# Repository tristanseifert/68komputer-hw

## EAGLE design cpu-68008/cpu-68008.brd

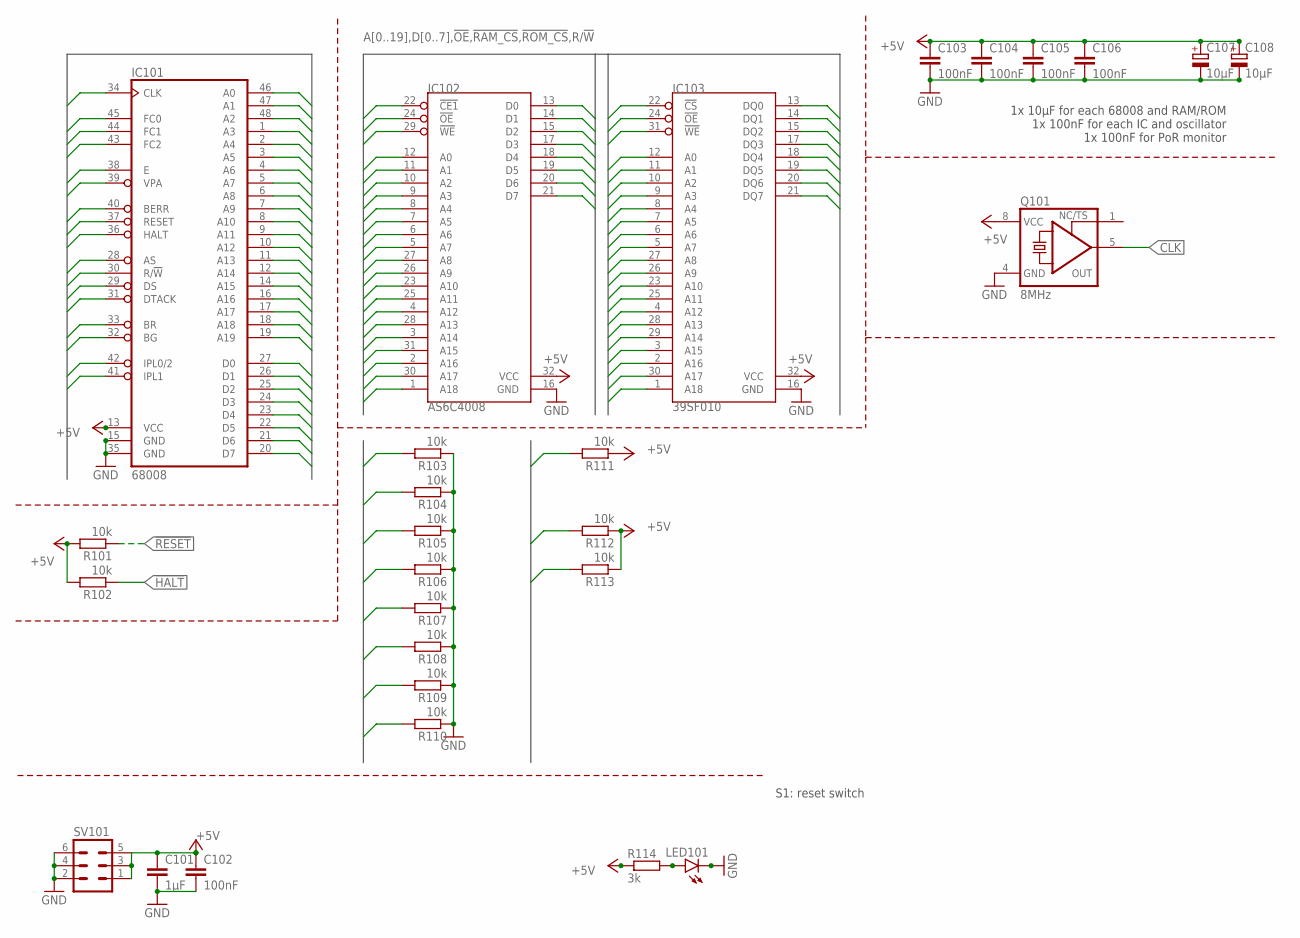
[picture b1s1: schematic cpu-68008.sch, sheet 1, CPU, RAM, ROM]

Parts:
C101: 1µF; C0805; MOUSER 710-885012107015
C102, C103, C104, C105, C106: 100nF; C0805; MOUSER 710-885012207072
C107, C108: 10µF; SMC_B; MOUSER 581-TAJB106K020RNJV
IC101: 68008; DIL48; MOUSER_SOCKET 517-4848-6004-CP
IC102: AS6C4008; DIL32; MOUSER_SOCKET 517-4832-6000-CP
IC103: 39SF010; DIL32; MOUSER 804-39SF010A7CPHE
LED101: LEDCHIPLED_1206; CHIPLED_1206; MOUSER 710-156120YS75300
Q101: 8MHz; DIL08S; MOUSER 774-MXO45HS-3C-8.0
R101, R102, R103, R104, R105, R106, R107, R108, R109, R110, R111, R112, R113: 10k; R2012; MOUSER 652-CR0805FX-1002ELF
R114: 3k; R2012; MOUSER 652-CR0805JW-302ELF
SV101: MA03-2

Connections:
!AS: IC101.28 (AS); also elsewhere on the board
!BERR: IC101.40 (BERR), R113.2; also elsewhere on the board
!BG: IC101.32 (BG); also elsewhere on the board
!BR: IC101.33 (BR), R111.2; also elsewhere on the board
!DS: IC101.29 (DS); also elsewhere on the board
!DTACK: IC101.31 (DTACK); also elsewhere on the board
!HALT: IC101.36 (HALT), R102.1; also elsewhere on the board
!IPL0/2: IC101.42 (IPL0/2); also elsewhere on the board
!IPL1: IC101.41 (IPL1); also elsewhere on the board
!OE: IC102.24 (!OE), IC103.24 (!OE); also elsewhere on the board
!RAM_CS: IC102.22 (!CE1); also elsewhere on the board
!RESET: IC101.37 (RESET), R101.1; also elsewhere on the board
!ROM_CS: IC103.22 (!CS); also elsewhere on the board
!VPA: IC101.39 (VPA), R112.2; also elsewhere on the board
+5V: C101.1, C102.1, C103.1, C104.1, C105.1, C106.1, C107.+, C108.+, IC101.13 (VCC), IC102.32 (VCC), IC103.32 (VCC), Q101.8 (VCC), R101.2, R102.2, R111.1, R112.1, R113.1, R114.1, SV101.1, SV101.3, SV101.5; also elsewhere on the board
A0: IC101.46 (A0), IC102.12 (A0), IC103.12 (A0); also elsewhere on the board
A1: IC101.47 (A1), IC102.11 (A1), IC103.11 (A1); also elsewhere on the board
A2: IC101.48 (A2), IC102.10 (A2), IC103.10 (A2); also elsewhere on the board
A3: IC101.1 (A3), IC102.9 (A3), IC103.9 (A3); also elsewhere on the board
A4: IC101.2 (A4), IC102.8 (A4), IC103.8 (A4); also elsewhere on the board
A5: IC101.3 (A5), IC102.7 (A5), IC103.7 (A5); also elsewhere on the board
A6: IC101.4 (A6), IC102.6 (A6), IC103.6 (A6); also elsewhere on the board
A7: IC101.5 (A7), IC102.5 (A7), IC103.5 (A7); also elsewhere on the board
A8: IC101.6 (A8), IC102.27 (A8), IC103.27 (A8); also elsewhere on the board
A9: IC101.7 (A9), IC102.26 (A9), IC103.26 (A9); also elsewhere on the board
A10: IC101.8 (A10), IC102.23 (A10), IC103.23 (A10); also elsewhere on the board
A11: IC101.9 (A11), IC102.25 (A11), IC103.25 (A11); also elsewhere on the board
A12: IC101.10 (A12), IC102.4 (A12), IC103.4 (A12); also elsewhere on the board
A13: IC101.11 (A13), IC102.28 (A13), IC103.28 (A13); also elsewhere on the board
A14: IC101.12 (A14), IC102.3 (A14), IC103.29 (A14); also elsewhere on the board
A15: IC101.14 (A15), IC102.31 (A15), IC103.3 (A15); also elsewhere on the board
A16: IC101.16 (A16), IC102.2 (A16), IC103.2 (A16); also elsewhere on the board
A17: IC101.17 (A17), IC102.30 (A17), IC103.30 (A17); also elsewhere on the board
A18: IC101.18 (A18), IC102.1 (A18), IC103.1 (A18); also elsewhere on the board
A19: IC101.19 (A19); also elsewhere on the board
CLK: IC101.34 (CLK), Q101.5 (OUT); also elsewhere on the board
D0: IC101.27 (D0), IC102.13 (D0), IC103.13 (DQ0), R103.2; also elsewhere on the board
D1: IC101.26 (D1), IC102.14 (D1), IC103.14 (DQ1), R104.2; also elsewhere on the board
D2: IC101.25 (D2), IC102.15 (D2), IC103.15 (DQ2), R105.2; also elsewhere on the board
D3: IC101.24 (D3), IC102.17 (D3), IC103.17 (DQ3), R106.2; also elsewhere on the board
D4: IC101.23 (D4), IC102.18 (D4), IC103.18 (DQ4), R107.2; also elsewhere on the board
D5: IC101.22 (D5), IC102.19 (D5), IC103.19 (DQ5), R108.2; also elsewhere on the board
D6: IC101.21 (D6), IC102.20 (D6), IC103.20 (DQ6), R109.2; also elsewhere on the board
D7: IC101.20 (D7), IC102.21 (D7), IC103.21 (DQ7), R110.2; also elsewhere on the board
E: IC101.38 (E); also elsewhere on the board
FC0: IC101.45 (FC0); also elsewhere on the board
FC1: IC101.44 (FC1); also elsewhere on the board
FC2: IC101.43 (FC2); also elsewhere on the board
GND: C101.2, C102.2, C103.2, C104.2, C105.2, C106.2, C107.-, C108.-, IC101.15 (GND), IC101.35 (GND), IC102.16 (GND), IC103.16 (GND), LED101.C, Q101.4 (GND), R103.1, R104.1, R105.1, R106.1, R107.1, R108.1, R109.1, R110.1, SV101.2, SV101.4, SV101.6; also elsewhere on the board
unnamed: LED101.A, R114.2
R/!W!: IC101.30 (R/!W), IC102.29 (!WE), IC103.31 (!WE); also elsewhere on the board

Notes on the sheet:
1x 10µF for each 68008 and RAM/ROM 1x 100nF for each IC and oscillator 1x 100nF for PoR monitor
S1: reset switch

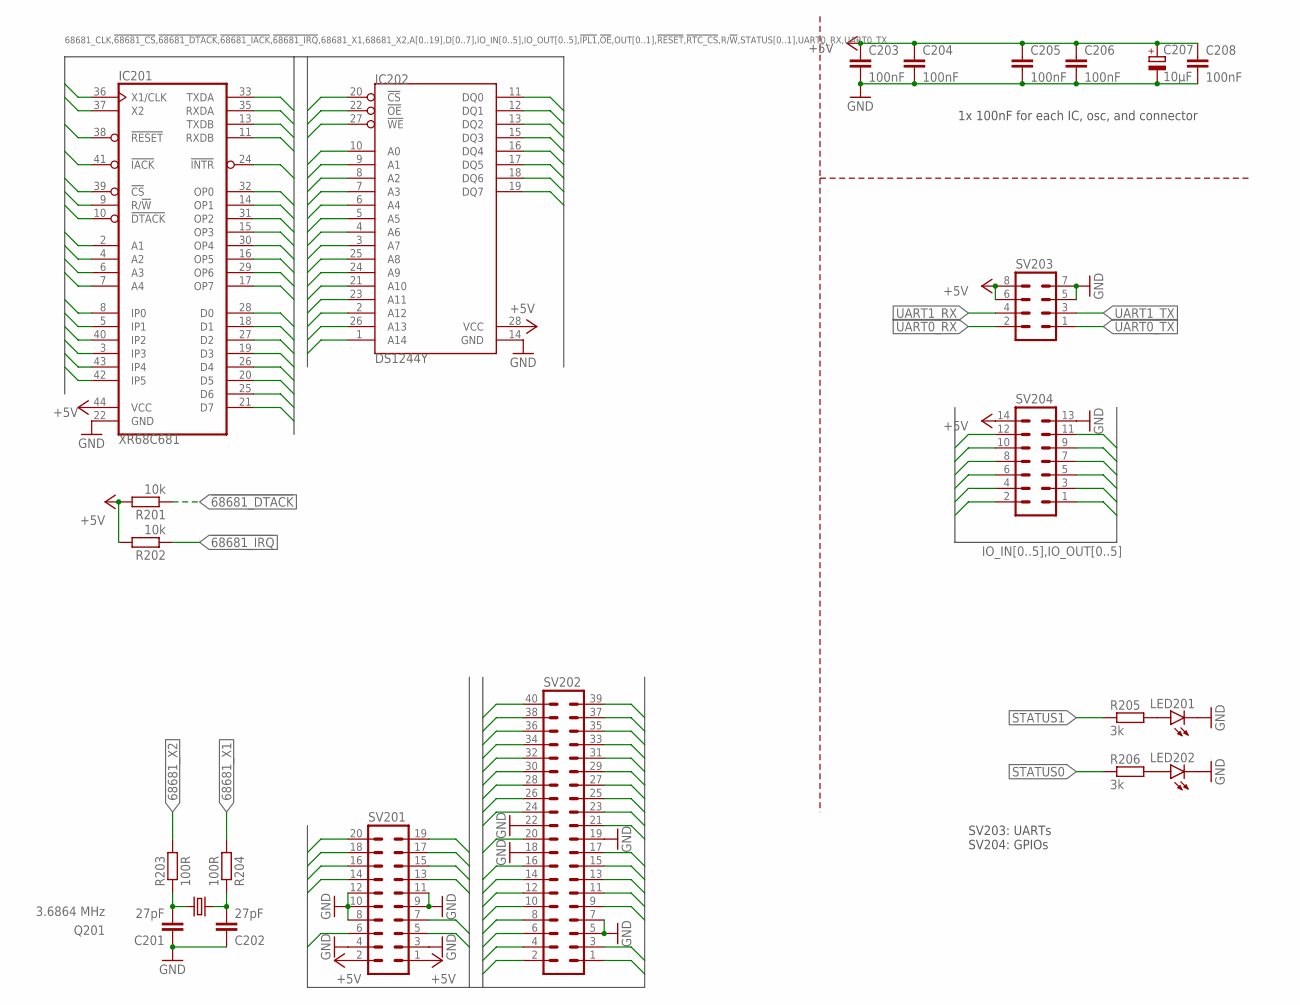
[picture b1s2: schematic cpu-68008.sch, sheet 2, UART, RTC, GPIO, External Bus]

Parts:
C201, C202: 27pF; C0805; MOUSER 80-C0805C270K5HACTU
C203, C204, C205, C206, C208: 100nF; C0805; MOUSER 710-885012207072
C207: 10µF; SMC_B; MOUSER 581-TAJB106K020RNJV
IC201: XR68C681; PLCC-S44; MOUSER 701-XR68C681CJ-F
IC202: DS1244Y; DIL28-6; MOUSER_SOCKET 571-1-2199299-2
LED201, LED202: LEDCHIPLED_1206; CHIPLED_1206; MOUSER 710-156120VS75300
Q201: 3.6864 MHz; HC49/S; MOUSER 815-ABL-3.6864-B2
R201, R202: 10k; R2012; MOUSER 652-CR0805FX-1002ELF
R203, R204: 100R; R2012; MOUSER 652-CR0805FX-1000ELF
R205, R206: 3k; R2012; MOUSER 652-CR0805JW-302ELF
SV201: MA10-2W
SV202: MA20-2W
SV203: MA04-2
SV204: MA07-2

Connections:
68681_X1: IC201.36 (X1/CLK), R204.2
68681_X2: IC201.37 (X2), R203.2
!68681_CS: IC201.39 (!CS); also elsewhere on the board
!68681_DTACK: IC201.10 (!DTACK), R201.1; also elsewhere on the board
!68681_IACK: IC201.41 (!IACK); also elsewhere on the board
!68681_IRQ: IC201.24 (!INTR), R202.1; also elsewhere on the board
!AS: SV202.33; also elsewhere on the board
!BERR: SV202.9; also elsewhere on the board
!BG: SV202.25; also elsewhere on the board
!BR: SV202.23; also elsewhere on the board
!BUS_CS: SV201.7; also elsewhere on the board
!BUS_DTACK: SV201.6; also elsewhere on the board
!BUS_IRQ: SV201.5; also elsewhere on the board
!DS: SV202.31; also elsewhere on the board
!DTACK: SV202.27; also elsewhere on the board
!HALT: SV202.17; also elsewhere on the board
!OE: IC202.22 (!OE); also elsewhere on the board
!RESET: IC201.38 (!RESET), SV202.15; also elsewhere on the board
!RTC_CS: IC202.20 (!CS); also elsewhere on the board
!VPA: SV202.11; also elsewhere on the board
+5V: C203.1, C204.1, C205.1, C206.1, C207.+, C208.1, IC201.44 (VCC), IC202.28 (VCC), R201.2, R202.2, SV201.1, SV201.2, SV203.6, SV203.8, SV204.14; also elsewhere on the board
A0: IC201.2 (A1), IC202.10 (A0), SV201.17; also elsewhere on the board
A1: IC201.4 (A2), IC202.9 (A1), SV201.15; also elsewhere on the board
A2: IC201.6 (A3), IC202.8 (A2), SV201.13; also elsewhere on the board
A3: IC201.7 (A4), IC202.7 (A3), SV201.14; also elsewhere on the board
A4: IC202.6 (A4), SV201.16; also elsewhere on the board
A5: IC202.5 (A5), SV201.18; also elsewhere on the board
A6: IC202.4 (A6), SV201.20; also elsewhere on the board
A7: IC202.3 (A7), SV202.2; also elsewhere on the board
A8: IC202.25 (A8), SV202.4; also elsewhere on the board
A9: IC202.24 (A9), SV202.6; also elsewhere on the board
A10: IC202.21 (A10), SV202.8; also elsewhere on the board
A11: IC202.23 (A11), SV202.10; also elsewhere on the board
A12: IC202.2 (A12), SV202.12; also elsewhere on the board
A13: IC202.26 (A13), SV202.14; also elsewhere on the board
A14: IC202.1 (A14), SV202.16; also elsewhere on the board
A15: SV202.20; also elsewhere on the board
A16: SV202.24; also elsewhere on the board
A17: SV202.26; also elsewhere on the board
A18: SV202.28; also elsewhere on the board
A19: SV202.30; also elsewhere on the board
CLK: SV202.21; also elsewhere on the board
D0: IC201.28 (D0), IC202.11 (DQ0), SV202.35; also elsewhere on the board
D1: IC201.18 (D1), IC202.12 (DQ1), SV202.37; also elsewhere on the board
D2: IC201.27 (D2), IC202.13 (DQ2), SV202.39; also elsewhere on the board
D3: IC201.19 (D3), IC202.15 (DQ3), SV202.40; also elsewhere on the board
D4: IC201.26 (D4), IC202.16 (DQ4), SV202.38; also elsewhere on the board
D5: IC201.20 (D5), IC202.17 (DQ5), SV202.36; also elsewhere on the board
D6: IC201.25 (D6), IC202.18 (DQ6), SV202.34; also elsewhere on the board
D7: IC201.21 (D7), IC202.19 (DQ7), SV202.32; also elsewhere on the board
E: SV202.13; also elsewhere on the board
FC0: SV201.19; also elsewhere on the board
FC1: SV202.1; also elsewhere on the board
FC2: SV202.3; also elsewhere on the board
GND: C201.1, C202.1, C203.2, C204.2, C205.2, C206.2, C207.-, C208.2, IC201.22 (GND), IC202.14 (GND), LED201.C, LED202.C, SV201.3, SV201.4, SV201.8, SV201.9, SV201.10, SV201.11, SV201.12, SV202.5, SV202.7, SV202.18, SV202.19, SV202.22, SV203.5, SV203.7, SV204.13; also elsewhere on the board
IO_IN0: IC201.40 (IP2), SV204.12
IO_IN1: IC201.42 (IP5), SV204.10
IO_IN2: IC201.43 (IP4), SV204.8
IO_IN3: IC201.3 (IP3), SV204.6
IO_IN4: IC201.5 (IP1), SV204.4
IO_IN5: IC201.8 (IP0), SV204.2
IO_OUT0: IC201.31 (OP2), SV204.11
IO_OUT1: IC201.32 (OP0), SV204.9
IO_OUT2: IC201.29 (OP6), SV204.7
IO_OUT3: IC201.30 (OP4), SV204.5
IO_OUT4: IC201.14 (OP1), SV204.3
IO_OUT5: IC201.16 (OP5), SV204.1
unnamed: C202.2, Q201.1, R204.1
unnamed: C201.2, Q201.2, R203.1
unnamed: LED201.A, R205.2
unnamed: LED202.A, R206.2
R/!W!: IC201.9 (R/!W), IC202.27 (!WE), SV202.29; also elsewhere on the board
STATUS0: IC201.15 (OP3), R206.1
STATUS1: IC201.17 (OP7), R205.1
UART0_RX: IC201.35 (RXDA), SV203.2
UART0_TX: IC201.33 (TXDA), SV203.1
UART1_RX: IC201.11 (RXDB), SV203.4
UART1_TX: IC201.13 (TXDB), SV203.3

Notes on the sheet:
1x 100nF for each IC, osc, and connector
SV203: UARTs SV204: GPIOs

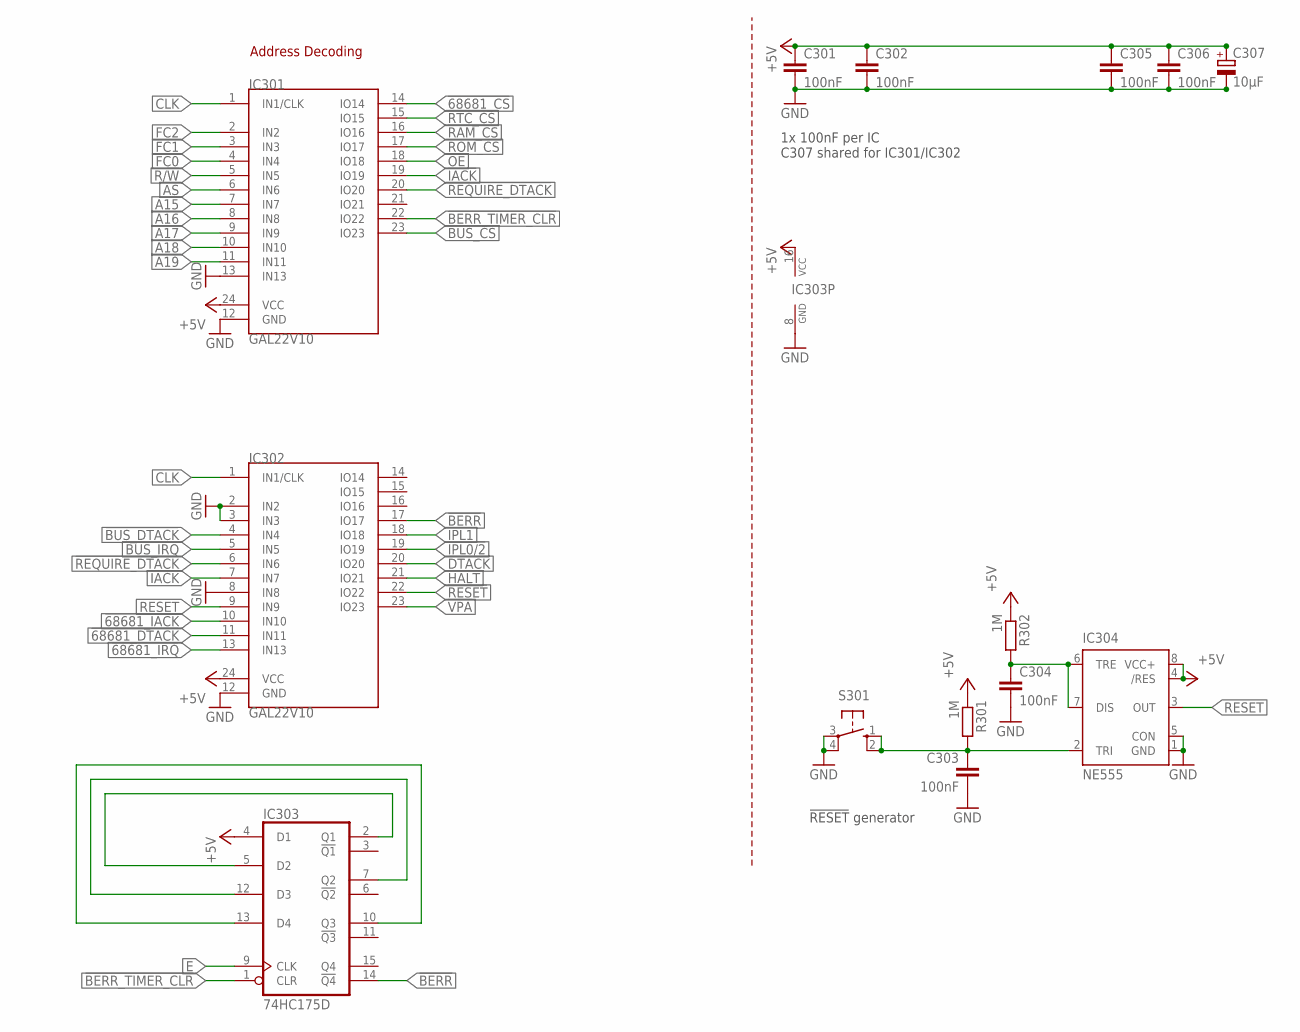
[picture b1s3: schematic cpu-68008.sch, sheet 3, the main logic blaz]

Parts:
C301, C302, C303, C305, C306: 100nF; C0805; MOUSER 710-885012207072
C304: 100nF; C0805; MOUSER 710-885012207078
C307: 10µF; SMC_B; MOUSER 581-TAJB106K020RNJV
IC301, IC302: GAL22V10; DIL24S
IC303: 74HC175D; SO16
IC304: NE555; DIL-08; MOUSER 595-NE555P
R301, R302: 1M; R2012; MOUSER 652-CR0805FX-18R2ELF
S301: 10-XX; B3F-10XX; MOUSER 653-B3F-1052

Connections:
!68681_CS: IC301.14 (IO14); also elsewhere on the board
!68681_DTACK: IC302.11 (IN11); also elsewhere on the board
!68681_IACK: IC302.10 (IN10); also elsewhere on the board
!68681_IRQ: IC302.13 (IN13); also elsewhere on the board
!AS: IC301.6 (IN6); also elsewhere on the board
!BERR: IC302.17 (IO17), IC303.14 (!Q4); also elsewhere on the board
!BERR_TIMER_CLR: IC301.22 (IO22), IC303.1 (CLR)
!BUS_CS: IC301.23 (IO23); also elsewhere on the board
!BUS_DTACK: IC302.4 (IN4); also elsewhere on the board
!BUS_IRQ: IC302.5 (IN5); also elsewhere on the board
!DTACK: IC302.20 (IO20); also elsewhere on the board
!HALT: IC302.21 (IO21); also elsewhere on the board
!IACK: IC301.19 (IO19), IC302.7 (IN7)
!IPL0/2: IC302.19 (IO19); also elsewhere on the board
!IPL1: IC302.18 (IO18); also elsewhere on the board
!OE: IC301.18 (IO18); also elsewhere on the board
!RAM_CS: IC301.16 (IO16); also elsewhere on the board
!REQUIRE_DTACK: IC301.20 (IO20), IC302.6 (IN6)
!RESET: IC302.22 (IO22); also elsewhere on the board
!ROM_CS: IC301.17 (IO17); also elsewhere on the board
!RTC_CS: IC301.15 (IO15); also elsewhere on the board
!VPA: IC302.23 (IO23); also elsewhere on the board
+5V: C301.1, C302.1, C305.1, C306.1, C307.+, IC301.24 (VCC), IC302.24 (VCC), IC303.4 (D1), IC303.16 (VCC), IC304.4 (/RES), IC304.8 (VCC+), R301.1, R302.1; also elsewhere on the board
A15: IC301.7 (IN7); also elsewhere on the board
A16: IC301.8 (IN8); also elsewhere on the board
A17: IC301.9 (IN9); also elsewhere on the board
A18: IC301.10 (IN10); also elsewhere on the board
A19: IC301.11 (IN11); also elsewhere on the board
CLK: IC301.1 (IN1/CLK), IC302.1 (IN1/CLK); also elsewhere on the board
E: IC303.9 (CLK); also elsewhere on the board
FC0: IC301.4 (IN4); also elsewhere on the board
FC1: IC301.3 (IN3); also elsewhere on the board
FC2: IC301.2 (IN2); also elsewhere on the board
GND: C301.2, C302.2, C303.2, C304.2, C305.2, C306.2, C307.-, IC301.12 (GND), IC301.13 (IN13), IC302.2 (IN2), IC302.3 (IN3), IC302.8 (IN8), IC302.12 (GND), IC303.8 (GND), IC304.1 (GND), IC304.5 (CON), S301.3, S301.4 (P1); also elsewhere on the board
unnamed: C303.1, IC304.2 (TRI), R301.2, S301.1 (S), S301.2 (S1)
unnamed: IC303.2 (Q1), IC303.5 (D2)
unnamed: IC303.7 (Q2), IC303.12 (D3)
unnamed: IC303.10 (Q3), IC303.13 (D4)
unnamed: C304.1, IC304.6 (TRE), IC304.7 (DIS), R302.2
R/!W!: IC301.5 (IN5); also elsewhere on the board
RESET: IC302.9 (IN9), IC304.3 (OUT)

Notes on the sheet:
!RESET! generator
1x 100nF per IC C307 shared for IC301/IC302
Address Decoding

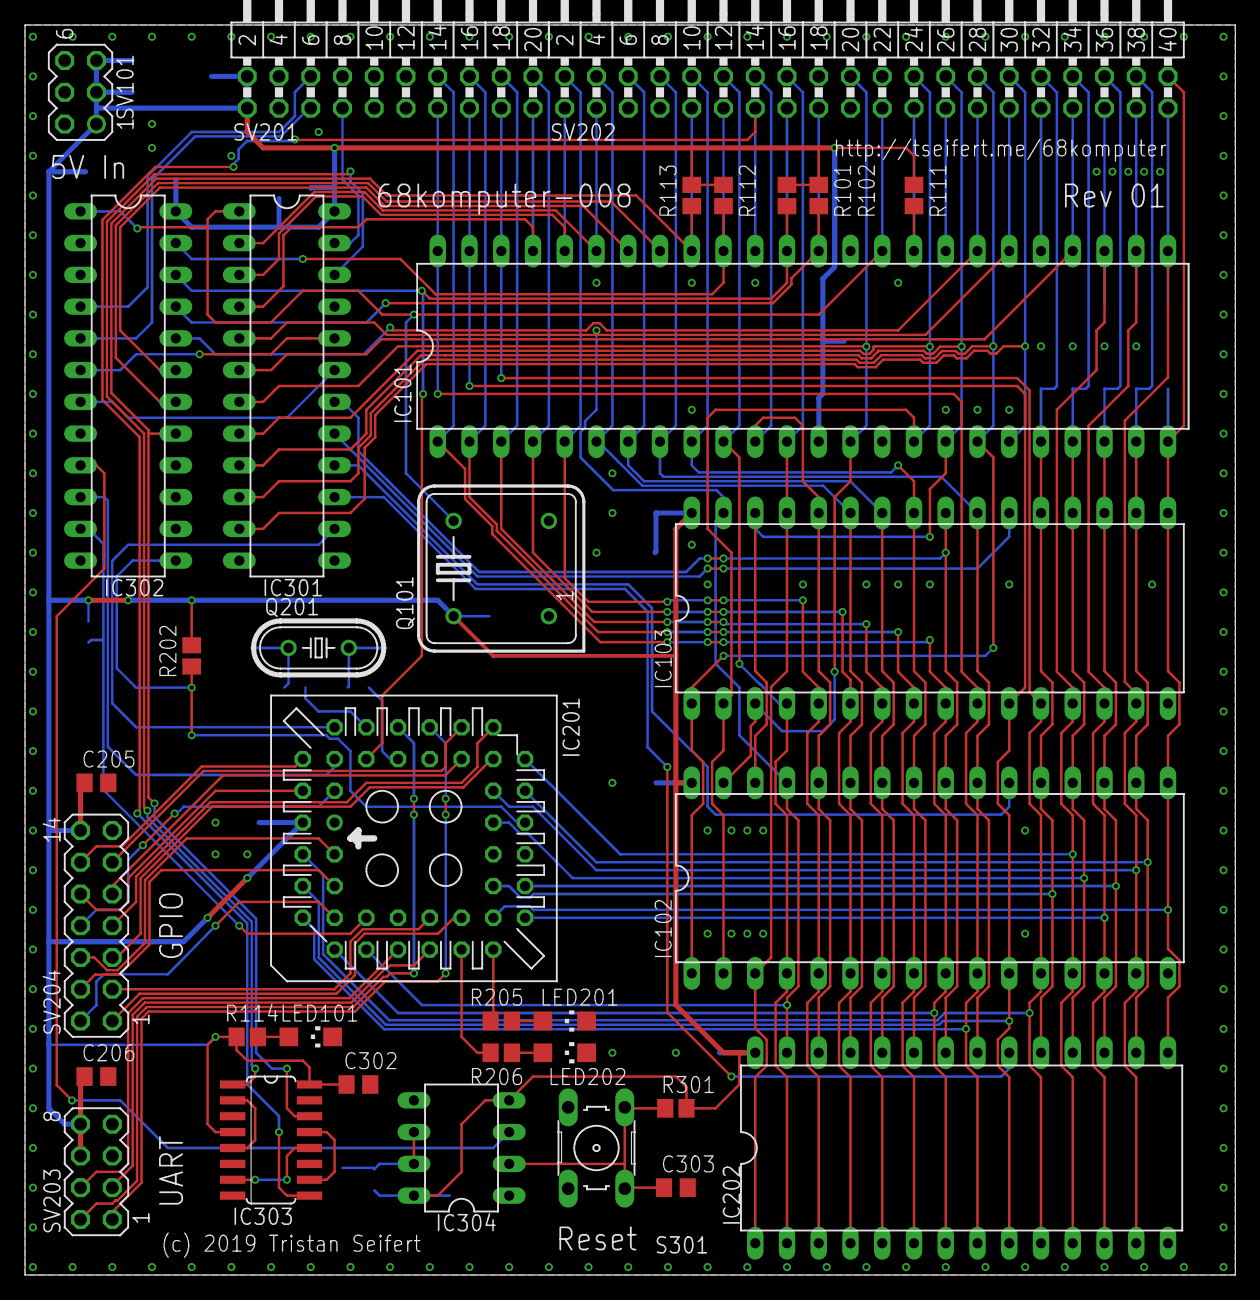
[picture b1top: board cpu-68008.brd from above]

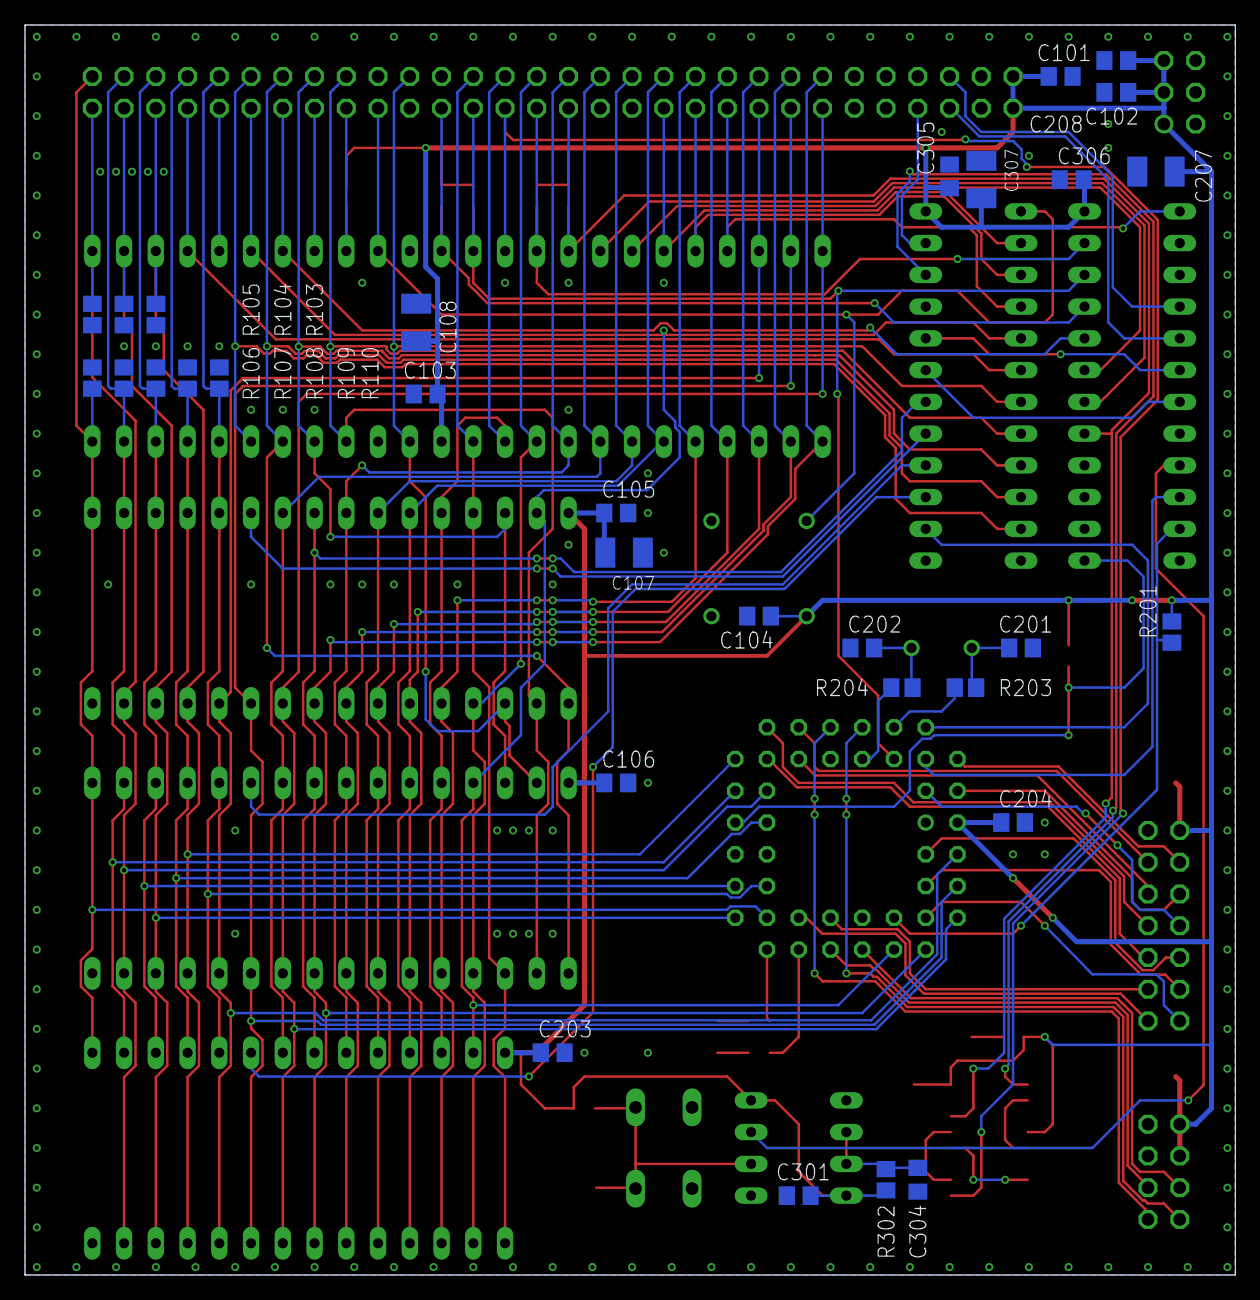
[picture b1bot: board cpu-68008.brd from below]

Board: 2 copper layers, 96.8 x 100.0 mm, 65 parts (31 on the bottom side), 92 nets.

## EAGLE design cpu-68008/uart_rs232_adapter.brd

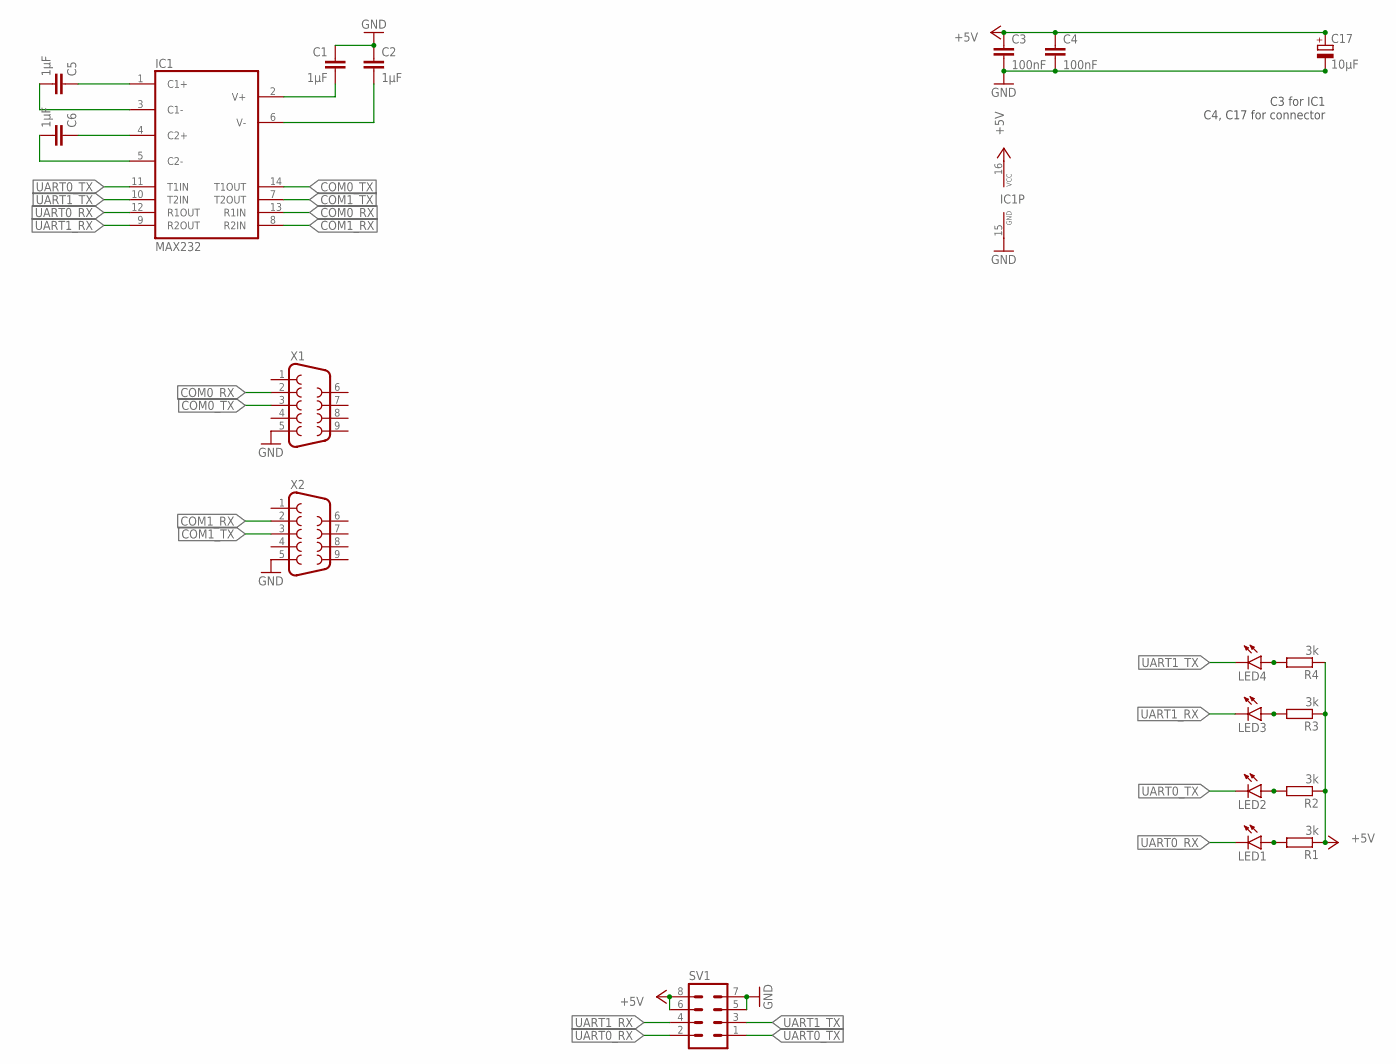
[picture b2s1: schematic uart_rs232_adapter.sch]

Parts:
C1, C2, C5, C6: 1µF; C0805; MOUSER 710-885012207078
C3, C4: 100nF; C0805; MOUSER 710-885012207072
C17: 10µF; SMC_B; MOUSER 581-TAJB106K020RNJV
IC1: MAX232; DIL16
LED1, LED2, LED3, LED4: LEDCHIPLED_1206; CHIPLED_1206; MOUSER 710-156120YS75300
R1, R2, R3, R4: 3k; R2012; MOUSER 652-CR0805JW-302ELF
SV1: MA04-2
X1, X2: F09HP

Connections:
+5V: C3.1, C4.1, C17.+, IC1.16 (VCC), R1.1, R2.1, R3.1, R4.1, SV1.6, SV1.8
COM0_RX: IC1.13 (R1IN), X1.2
COM0_TX: IC1.14 (T1OUT), X1.3
COM1_RX: IC1.8 (R2IN), X2.2
COM1_TX: IC1.7 (T2OUT), X2.3
GND: C1.1, C2.1, C3.2, C4.2, C17.-, IC1.15 (GND), SV1.5, SV1.7, X1.5, X2.5
unnamed: LED1.A, R1.2
unnamed: LED2.A, R2.2
unnamed: LED3.A, R3.2
unnamed: LED4.A, R4.2
unnamed: C1.2, IC1.2 (V+)
unnamed: C2.2, IC1.6 (V-)
unnamed: C6.1, IC1.4 (C2+)
unnamed: C5.1, IC1.1 (C1+)
unnamed: C5.2, IC1.3 (C1-)
unnamed: C6.2, IC1.5 (C2-)
UART0_RX: IC1.12 (R1OUT), LED1.C, SV1.2
UART0_TX: IC1.11 (T1IN), LED2.C, SV1.1
UART1_RX: IC1.9 (R2OUT), LED3.C, SV1.4
UART1_TX: IC1.10 (T2IN), LED4.C, SV1.3

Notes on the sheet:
C3 for IC1 C4, C17 for connector

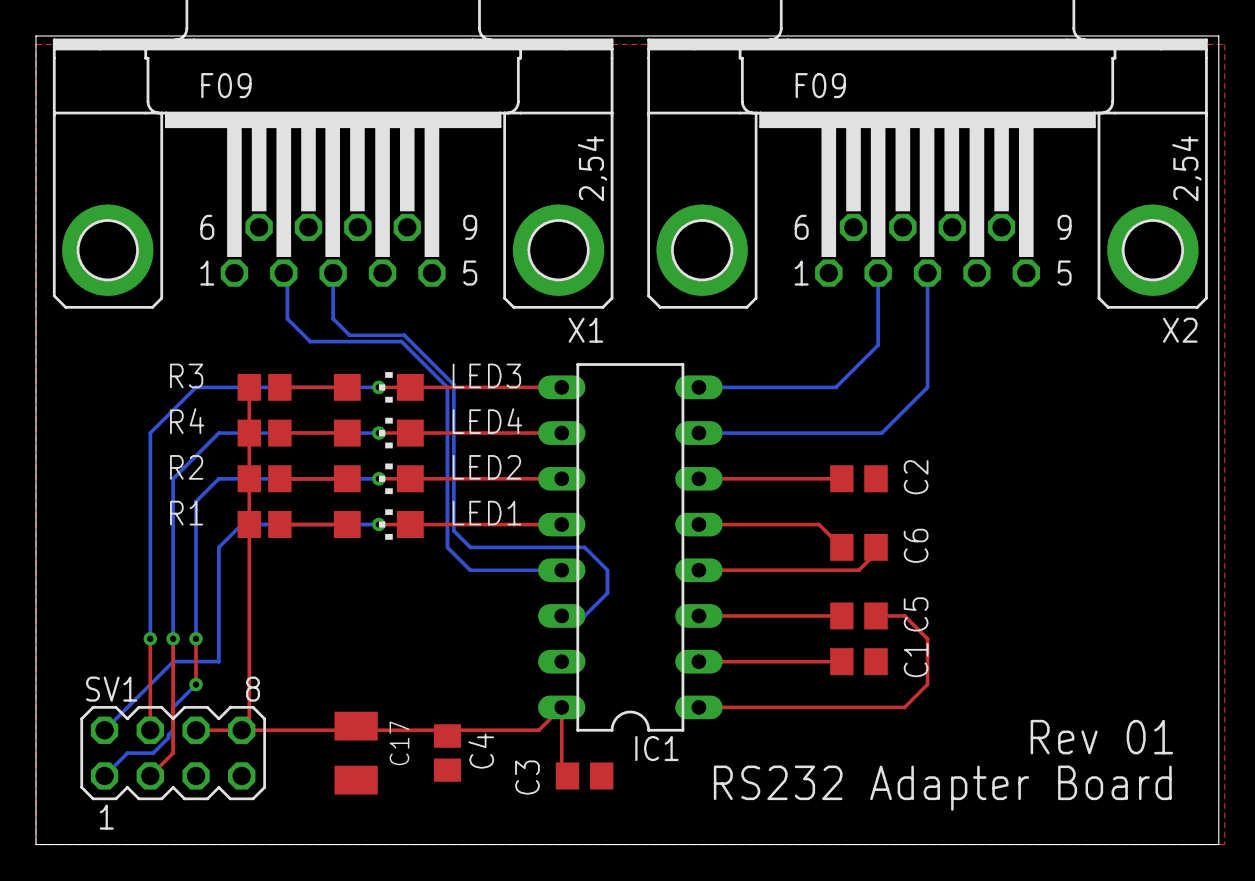
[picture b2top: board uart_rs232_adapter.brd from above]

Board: 2 copper layers, 65.7 x 44.9 mm, 19 parts (0 on the bottom side), 20 nets.

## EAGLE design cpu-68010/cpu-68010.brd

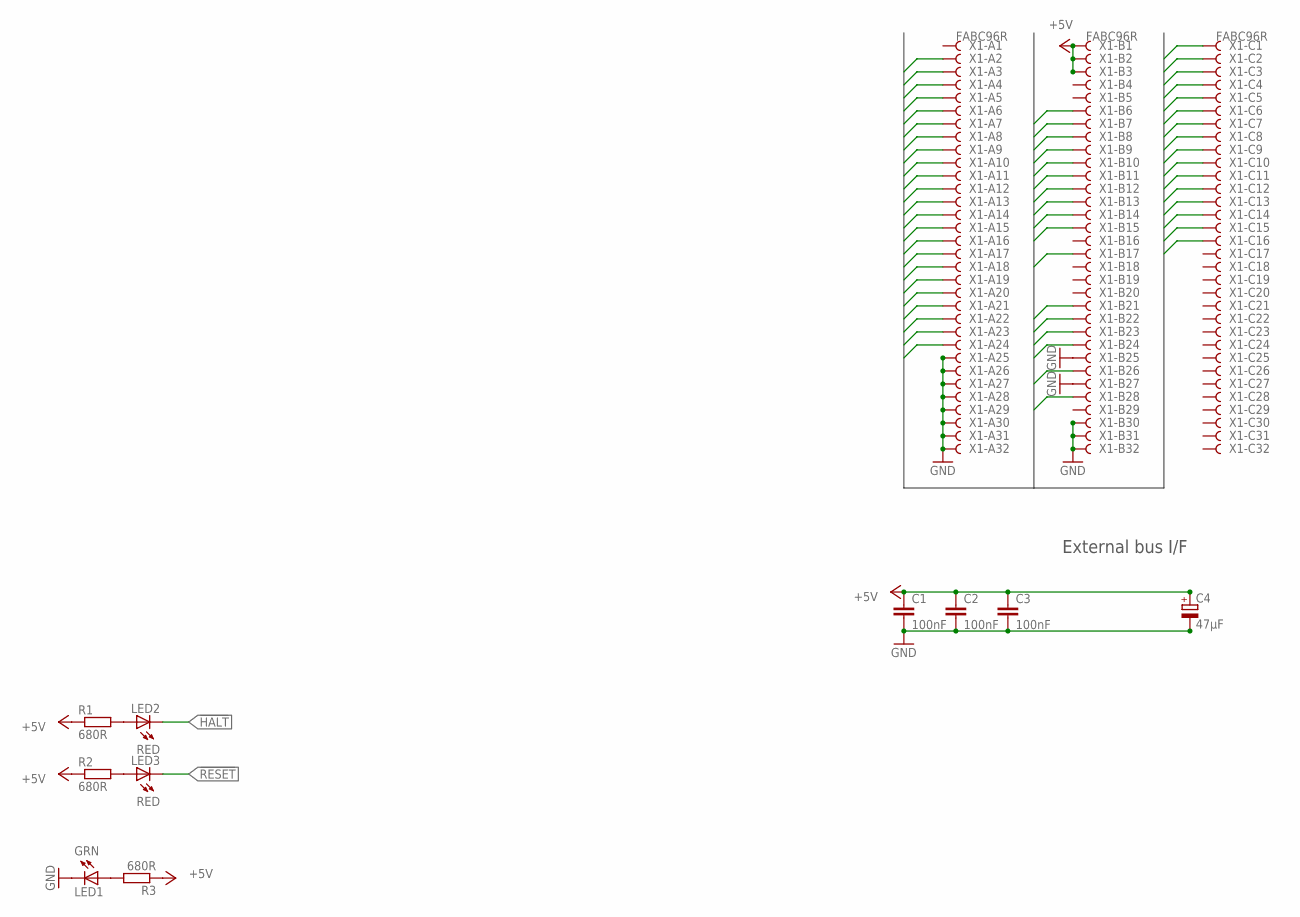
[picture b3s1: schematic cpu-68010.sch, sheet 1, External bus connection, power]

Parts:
C1, C2, C3: 100nF; C0805; MOUSER 710-885012207072
C4: 47µF; CT6032; MOUSER 581-TAJD476M016RNJV
LED1: GRN; CHIPLED_1206; MOUSER 604-APTR3216SGC
LED2, LED3: RED; CHIPLED_1206; MOUSER 710-156120RS75300
R1, R2, R3: 680R; M0805; MOUSER 652-CR0805-FX6800GLF
X1: FABC96R

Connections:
!AS: X1.B21; also elsewhere on the board
!BERR: X1.B9; also elsewhere on the board
!BG: X1.B14; also elsewhere on the board
!BGACK: X1.B15; also elsewhere on the board
!BR: X1.B13; also elsewhere on the board
!EXT_DTACK: X1.B28; also elsewhere on the board
!EXT_IRQ: X1.B17; also elsewhere on the board
!HALT: LED2.C, X1.B11; also elsewhere on the board
!LDS: X1.B24; also elsewhere on the board
!RESET: LED3.C, X1.B10; also elsewhere on the board
!UDS: X1.B23; also elsewhere on the board
!VPA: X1.B12; also elsewhere on the board
+5V: C1.1, C2.1, C3.1, C4.+, R1.1, R2.1, R3.1, X1.B1, X1.B2, X1.B3; also elsewhere on the board
A1: X1.A2; also elsewhere on the board
A2: X1.A3; also elsewhere on the board
A3: X1.A4; also elsewhere on the board
A4: X1.A5; also elsewhere on the board
A5: X1.A6; also elsewhere on the board
A6: X1.A7; also elsewhere on the board
A7: X1.A8; also elsewhere on the board
A8: X1.A9; also elsewhere on the board
A9: X1.A10; also elsewhere on the board
A10: X1.A11; also elsewhere on the board
A11: X1.A12; also elsewhere on the board
A12: X1.A13; also elsewhere on the board
A13: X1.A14; also elsewhere on the board
A14: X1.A15; also elsewhere on the board
A15: X1.A16; also elsewhere on the board
A16: X1.A17; also elsewhere on the board
A17: X1.A18; also elsewhere on the board
A18: X1.A19; also elsewhere on the board
A19: X1.A20; also elsewhere on the board
A20: X1.A21; also elsewhere on the board
A21: X1.A22; also elsewhere on the board
A22: X1.A23; also elsewhere on the board
A23: X1.A24; also elsewhere on the board
CLK: X1.B26; also elsewhere on the board
D0: X1.C1; also elsewhere on the board
D1: X1.C2; also elsewhere on the board
D2: X1.C3; also elsewhere on the board
D3: X1.C4; also elsewhere on the board
D4: X1.C5; also elsewhere on the board
D5: X1.C6; also elsewhere on the board
D6: X1.C7; also elsewhere on the board
D7: X1.C8; also elsewhere on the board
D8: X1.C9; also elsewhere on the board
D9: X1.C10; also elsewhere on the board
D10: X1.C11; also elsewhere on the board
D11: X1.C12; also elsewhere on the board
D12: X1.C13; also elsewhere on the board
D13: X1.C14; also elsewhere on the board
D14: X1.C15; also elsewhere on the board
D15: X1.C16; also elsewhere on the board
FC0: X1.B6; also elsewhere on the board
FC1: X1.B7; also elsewhere on the board
FC2: X1.B8; also elsewhere on the board
GND: C1.2, C2.2, C3.2, C4.-, LED1.C, X1.A25, X1.A26, X1.A27, X1.A28, X1.A29, X1.A30, X1.A31, X1.A32, X1.B25, X1.B27, X1.B30, X1.B31, X1.B32; also elsewhere on the board
unnamed: LED3.A, R2.2
unnamed: LED2.A, R1.2
unnamed: LED1.A, R3.2
R!W!: X1.B22; also elsewhere on the board

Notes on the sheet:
External bus I/F

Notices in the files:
cpu-68008/cpu-68008.brd:
(c) 2019 Tristan Seifert
